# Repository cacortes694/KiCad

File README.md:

# KiCad
Carlos Cortes' KiCad Repository for his personal projects and team projects

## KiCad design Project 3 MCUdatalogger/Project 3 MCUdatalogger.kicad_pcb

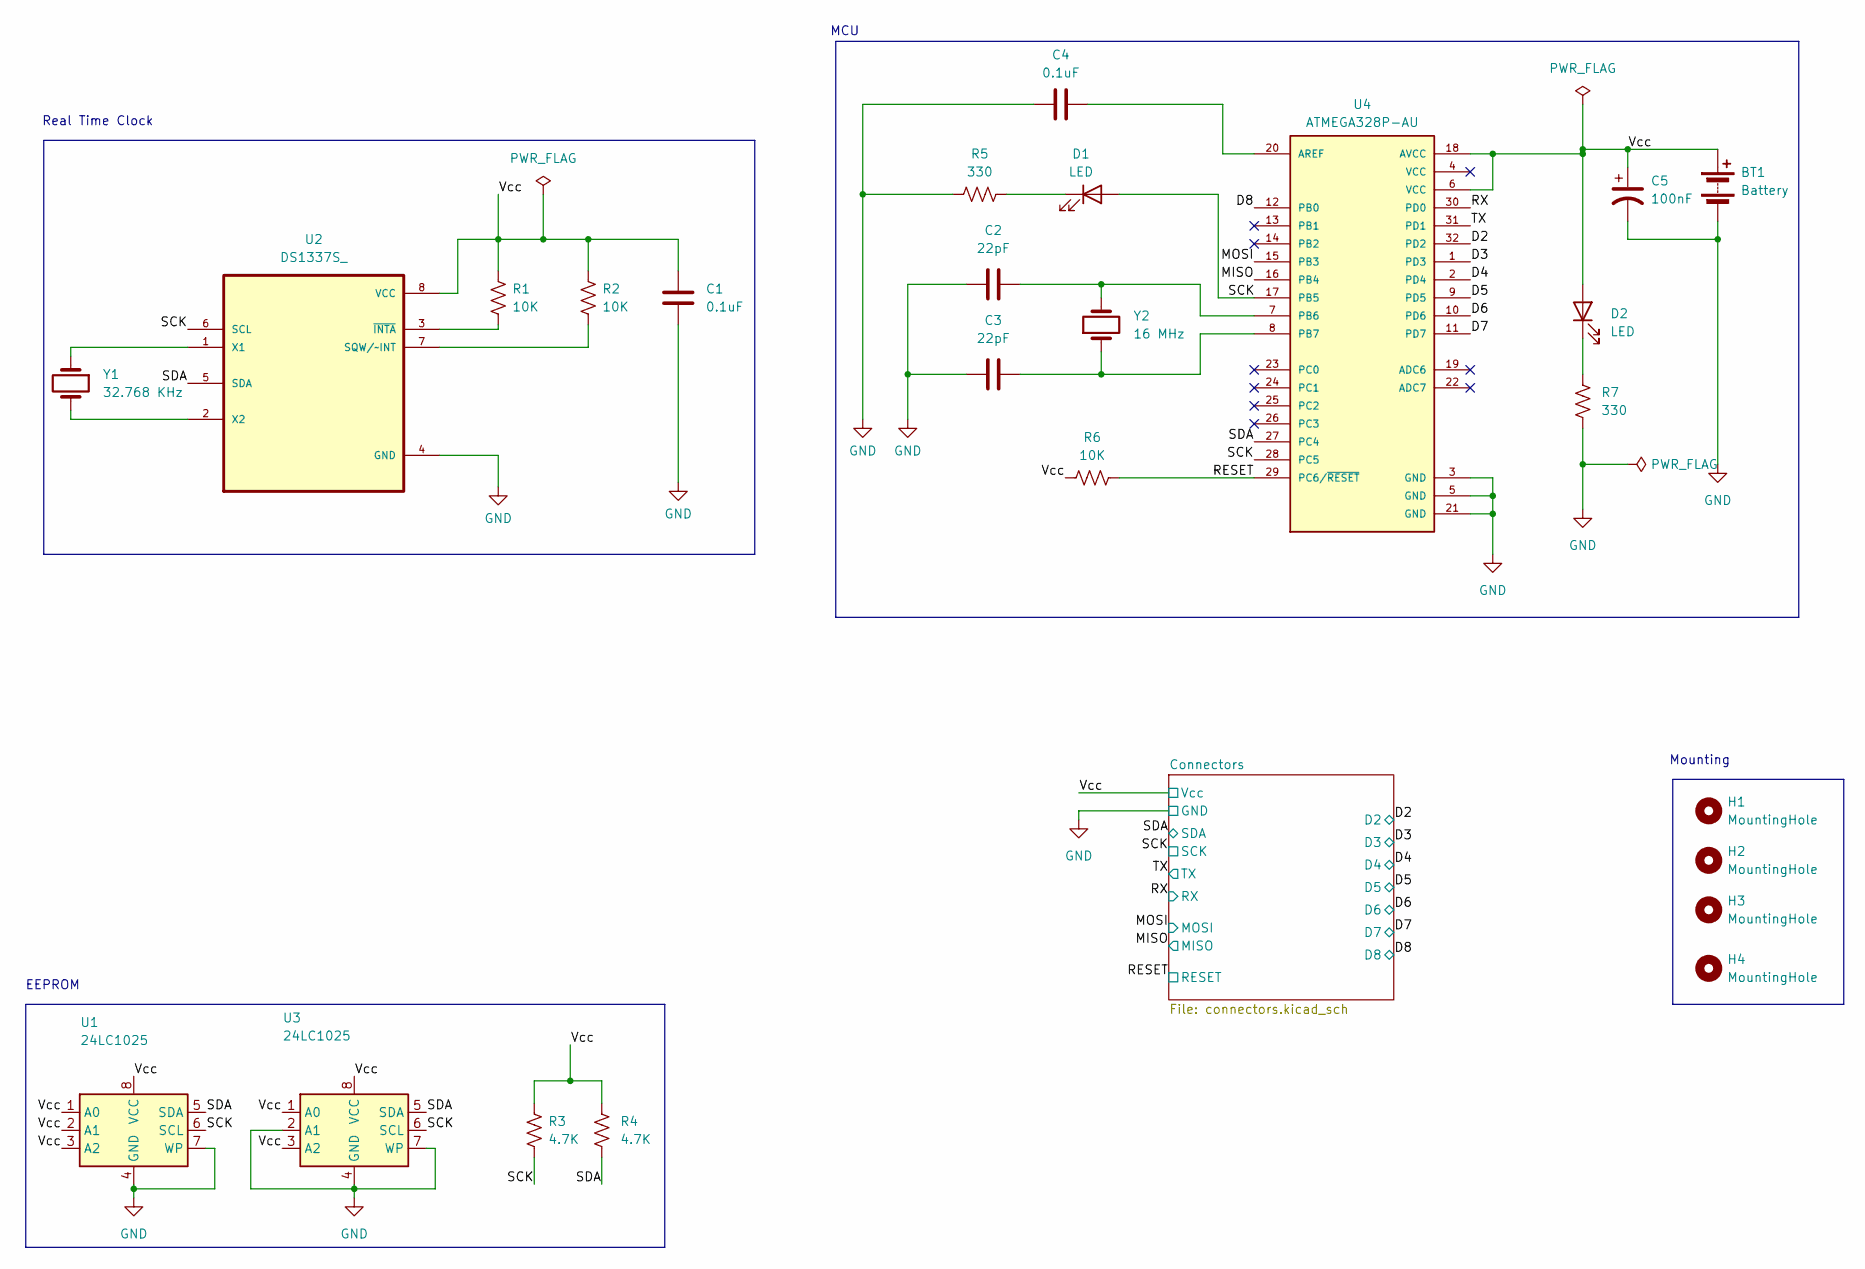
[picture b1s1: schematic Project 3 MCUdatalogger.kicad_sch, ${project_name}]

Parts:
BT1: Battery; PinHeader_1x02_P2.54mm_Vertical
C1, C4: 0.1uF; C_0805_2012Metric
C2, C3: 22pF; C_0805_2012Metric
C5: 100nF; C_0805_2012Metric
D1, D2: LED; LED_0805_2012Metric
H1, H2, H3, H4: MountingHole; MountingHole_2.1mm
R1, R2, R6: 10K; R_0805_2012Metric
R3, R4: 4.7K; R_0805_2012Metric
R5, R7: 330; R_0805_2012Metric
U1, U3: 24LC1025; SOIC-8_5.23x5.23mm_P1.27mm
U2: DS1337S_; SOIC127P600X175-8N
U4: ATMEGA328P-AU; QFP80P900X900X120-32N; PARTREV 8271A
Y1: 32.768 KHz; Crystal_SMD_Abracon_ABM3-2Pin_5.0x3.2mm_HandSoldering
Y2: 16 MHz; Crystal_SMD_Abracon_ABM3-2Pin_5.0x3.2mm_HandSoldering

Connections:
/D2: U4.32 (PD2); also elsewhere on the board
/D3: U4.1 (PD3); also elsewhere on the board
/D4: U4.2 (PD4); also elsewhere on the board
/D5: U4.9 (PD5); also elsewhere on the board
/D6: U4.10 (PD6); also elsewhere on the board
/D7: U4.11 (PD7); also elsewhere on the board
/D8: U4.12 (PB0); also elsewhere on the board
/MISO: U4.16 (PB4); also elsewhere on the board
/MOSI: U4.15 (PB3); also elsewhere on the board
/RESET: R6.2, U4.29 (PC6/~RESET); also elsewhere on the board
/RX: U4.30 (PD0); also elsewhere on the board
/SCK: D1.2 (A), R3.2, U1.6 (SCL), U2.6 (SCL), U3.6 (SCL), U4.17 (PB5), U4.28 (PC5); also elsewhere on the board
/SDA: R4.2, U1.5 (SDA), U2.5 (SDA), U3.5 (SDA), U4.27 (PC4); also elsewhere on the board
/TX: U4.31 (PD1); also elsewhere on the board
/Vcc: BT1.1 (+), C1.1, C5.1, D2.2 (A), R1.1, R2.1, R3.1, R4.1, R6.1, U1.1 (A0), U1.2 (A1), U1.3 (A2), U1.8 (VCC), U2.8 (VCC), U3.1 (A0), U3.3 (A2), U3.8 (VCC), U4.6 (VCC), U4.18 (AVCC); also elsewhere on the board
GND: BT1.2 (-), C1.2, C2.1, C3.1, C4.1, C5.2, R5.1, R7.2, U1.4 (GND), U1.7 (WP), U2.4 (GND), U3.2 (A1), U3.4 (GND), U3.7 (WP), U4.3 (GND), U4.5 (GND), U4.21 (GND); also elsewhere on the board
unnamed: D1.1 (K), R5.2
unnamed: D2.1 (K), R7.1
unnamed: R2.2, U2.7 (SQW/~INT)
unnamed: U2.1 (X1), Y1.1
unnamed: U2.2 (X2), Y1.2
unnamed: R1.2, U2.3 (~INTA)
unnamed: C4.2, U4.20 (AREF)
unnamed: C2.2, U4.7 (PB6), Y2.2
unnamed: C3.2, U4.8 (PB7), Y2.1

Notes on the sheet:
EEPROM
Mounting
MCU
Real Time Clock

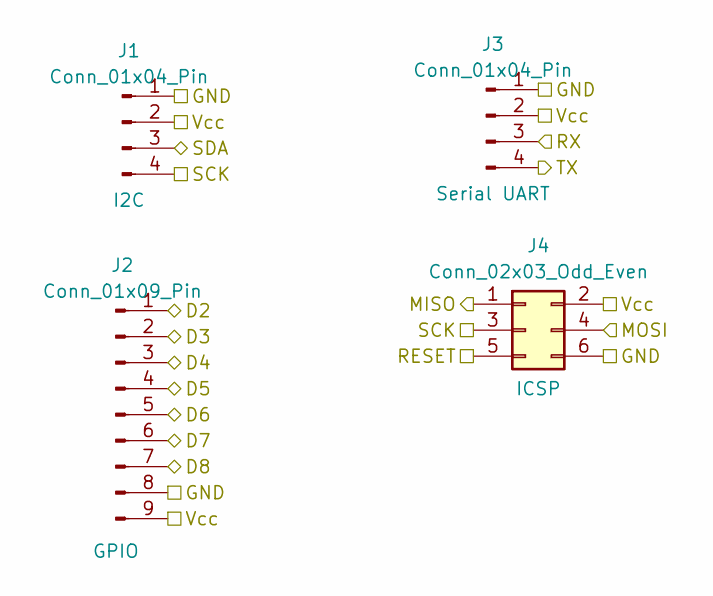
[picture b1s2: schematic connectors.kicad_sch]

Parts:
J1, J3: Conn_01x04_Pin; PinHeader_1x04_P2.54mm_Vertical
J2: Conn_01x09_Pin; PinHeader_1x09_P2.54mm_Vertical
J4: Conn_02x03_Odd_Even; PinHeader_2x03_P2.54mm_Vertical

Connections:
/D2: J2.1; also elsewhere on the board
/D3: J2.2; also elsewhere on the board
/D4: J2.3; also elsewhere on the board
/D5: J2.4; also elsewhere on the board
/D6: J2.5; also elsewhere on the board
/D7: J2.6; also elsewhere on the board
/D8: J2.7; also elsewhere on the board
/MISO: J4.1; also elsewhere on the board
/MOSI: J4.4; also elsewhere on the board
/RESET: J4.5; also elsewhere on the board
/RX: J3.3; also elsewhere on the board
/SCK: J1.4, J4.3; also elsewhere on the board
/SDA: J1.3; also elsewhere on the board
/TX: J3.4; also elsewhere on the board
/Vcc: J1.2, J2.9, J3.2, J4.2; also elsewhere on the board
GND: J1.1, J2.8, J3.1, J4.6; also elsewhere on the board

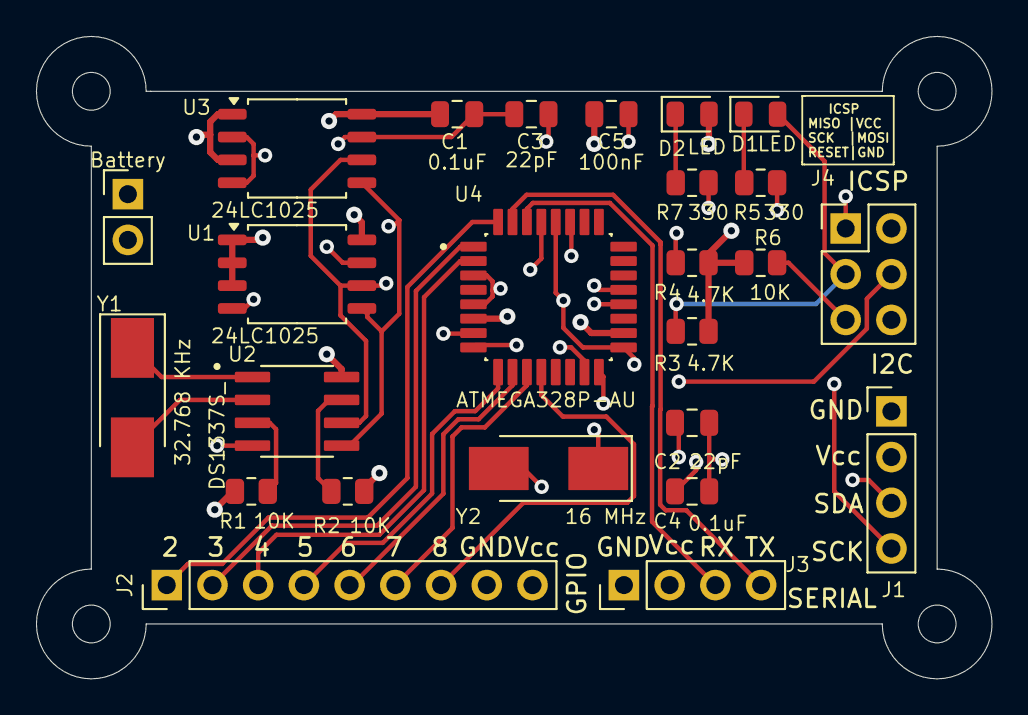
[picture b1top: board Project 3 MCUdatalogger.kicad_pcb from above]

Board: 4 copper layers, 53.1 x 35.7 mm, 29 parts (0 on the bottom side), 25 nets.

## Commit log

2024-11-27 First commit.
2024-11-27 Added Resistor
2024-11-27 Setup of EEschema for new project
2024-11-27 Have added the required symbols to the schematic sheets
2024-11-27 Change locations of symbols (arrange).
2024-11-27 Added component values
2024-11-27 Fixed Gitignore file
2024-11-27 Completed Symbol to footprint associations
2024-11-27 Completed wiring of main sheet.
2024-11-27 Completed wiring in the second sheet.
2024-11-27 updated .gitignore
2024-11-27 Allocated GND and Vcc nets to the Power net class.
2024-11-27 Completed Comments
2024-11-27 Setup Pcbnew.
2024-11-27 Complete Placement of Footprints.
2024-11-27 Routing sans GND Vcc complete.
2024-11-27 Completed routing
2024-11-27 Refined Routing Complete
2024-11-27 Fixed outstanding issues
2024-11-27 Added Finishing touches and Gerber Files
2024-11-27 completed 2_layer_pcb
2024-11-27 Fixed Merger
2024-11-27 Saved for the night
2024-11-27 Saved Part 2
2024-11-27 Added gerber file to git ignore
2024-11-27 Routing
2024-11-27 Added board characteristics
2024-11-27 fixing bugs
